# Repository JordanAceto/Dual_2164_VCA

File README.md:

# SSI2164 based dual VCA PCB

## [SCHEMATIC](https://github.com/JordanAceto/Dual_2164_VCA/blob/master/main_pcb/construction_docs/dual_VCA_schematic.pdf)

## Features:
- Two independent linear VCAs
- Manual offset controls
- Attenuated CV inputs
- Unity gain at +5 volts CV
- AC/DC coupling selected by solder jumper
- Designed to either use board mounted pots and jacks which affix directly to a panel, or mount to a bracket and wire by hand
- There is a 10hp pcb front panel, for a cheap and cheerful panel option.

## Status of the project:

Task | Status |
---------|--------------|
Schematic capture | &#9745;
PCB layout | &#9745;
Test build | &#9745;
Safe to order boards| &#9745;

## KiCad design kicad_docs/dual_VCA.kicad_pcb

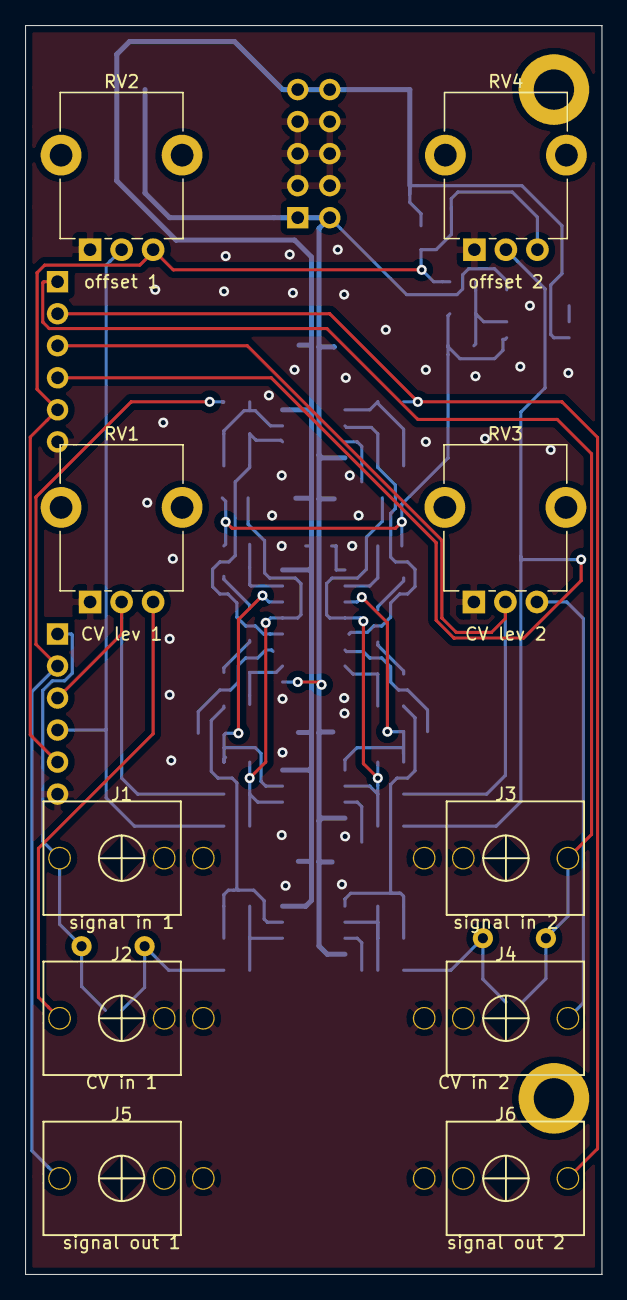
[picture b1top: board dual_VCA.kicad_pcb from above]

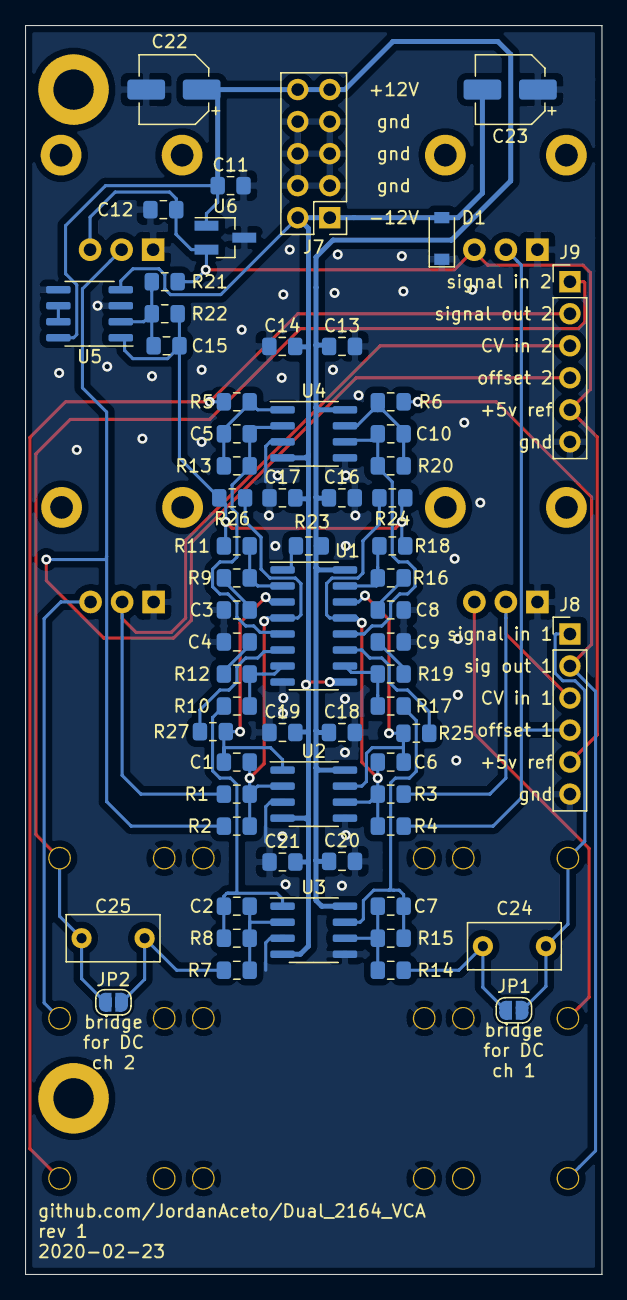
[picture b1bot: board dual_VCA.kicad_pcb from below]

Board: 2 copper layers, 45.7 x 99.1 mm, 74 parts (64 on the bottom side), 42 nets.

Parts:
C1, C5, C6, C10: 100pF; C_0805_2012Metric_Pad1.15x1.40mm_HandSolder
C2, C7: 22pF; C_0805_2012Metric_Pad1.15x1.40mm_HandSolder
C3, C4, C8, C9: 560pF; C_0805_2012Metric_Pad1.15x1.40mm_HandSolder
C11, C12, C13, C14, C15, C16, C17, C18, C19, C20, C21: 100nF; C_0805_2012Metric_Pad1.15x1.40mm_HandSolder
C22, C23: 10uF; CP_Elec_5x5.4
C24, C25: 470nF; C_Rect_L7.2mm_W3.5mm_P5.00mm_FKS2_FKP2_MKS2_MKP2
D1: BAT48; D_SOD-123
J1: signal_in_1; PJ301M-12
J2: CV_in_1; PJ301M-12
J3: signal_in_2; PJ301M-12
J4: CV_in_2; PJ301M-12
J5: signal_out_1; PJ301M-12
J6: signal_out_2; PJ301M-12
J7: power_input; PinHeader_2x05_P2.54mm_Vertical
J8, J9: Conn_01x06; PinHeader_1x06_P2.54mm_Vertical
JP1, JP2: AC/DC coupling; SolderJumper-2_P1.3mm_Open_RoundedPad1.0x1.5mm
R1, R2, R3, R4, R7, R8, R11, R14, R15, R18: 100k; R_0805_2012Metric_Pad1.15x1.40mm_HandSolder
R5, R6: 1k; R_0805_2012Metric_Pad1.15x1.40mm_HandSolder
R9, R12, R16, R19: 510; R_0805_2012Metric_Pad1.15x1.40mm_HandSolder
R10, R13, R17, R20: 30k; R_0805_2012Metric_Pad1.15x1.40mm_HandSolder
R21, R22: 10k; R_0805_2012Metric_Pad1.15x1.40mm_HandSolder
R23: R; R_0805_2012Metric_Pad1.15x1.40mm_HandSolder
R24, R26: 10M; R_0805_2012Metric_Pad1.15x1.40mm_HandSolder
R25, R27: 4k7; R_0805_2012Metric_Pad1.15x1.40mm_HandSolder
RV1, RV2, RV3, RV4: 100k; Potentiometer_Alpha_RD901F-40-00D_Single_Vertical_CircularH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
U1: SSM2164; SOIC-16_3.9x9.9mm_P1.27mm
U2, U3, U4, U5: TL072; SOIC-8_3.9x4.9mm_P1.27mm
U6: MAX6035xxUR50; SOT-23_Handsoldering

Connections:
+5VA: C12.1, J8.5, J9.5, R21.2, RV2.3, RV4.3, U6.2
+12V: C11.1, C13.1, C16.1, C18.1, C20.1, C22.1, J7.9, J7.10, R23.1, U1.16, U2.8, U3.8, U4.8, U5.8, U6.1
-5VA: C15.1, R11.2, R18.2, R22.1, R24.2, R26.2, U5.1
-12V: C14.2, C17.2, C19.2, C21.2, C23.2, D1.2, J7.1, J7.2, U1.9, U2.4, U3.4, U4.4, U5.4
/CV_in_1: J8.3, R3.2, RV1.2
/CV_in_2: J9.3, R1.2, RV3.2
/VCA_1/VCA_1_CV_summing_node_i_in: C6.2, R3.1, R4.1, R24.1, U1.13, U2.6
/VCA_1/VCA_1_signal_v_in: C24.1, JP1.2, R14.2
/VCA_1/VCA_1_signal_v_out: C10.1, R6.2, R20.1, U4.7
/VCA_2/VCA_2_CV_summing_node_i_in: C1.2, R1.1, R2.1, R26.1, U1.4, U2.2
/VCA_2/VCA_2_signal_v_in: C25.1, JP2.2, R7.2
/VCA_2/VCA_2_signal_v_out: C5.1, R5.2, R13.1, U4.1
/offset_in_1: J8.4, R4.2, RV2.2
/offset_in_2: J9.4, R2.2, RV4.2
/signal_in_1: C24.2, J1.3, J8.1, JP1.1
/signal_in_2: C25.2, J3.3, J9.1, JP2.1
/signal_out_1: J5.3, J8.2, R6.1
/signal_out_2: J6.3, J9.2, R5.1
GND: C3.2, C4.2, C8.2, C9.2, C11.2, C12.2, C13.2, C14.1, C16.2, C17.1, C18.2, C19.1, C20.2, C21.1, C22.2, C23.1, D1.1, J1.1, J1.2, J2.1, J2.2, J3.1, J3.2, J4.1, J4.2, J5.1, J6.1, J7.3, J7.4, J7.5, J7.6, J7.7, J7.8, J8.6, J9.6, RV1.1, RV2.1, RV3.1, RV4.1, U1.8, U2.3, U2.5, U3.3, U3.5, U4.3, U4.5, U5.3, U5.5, U6.3
unnamed: C1.1, R27.2, U1.3, U2.1
unnamed: C2.1, R8.1, R10.2, U3.1
unnamed: C2.2, R7.1, R8.2, U3.2
unnamed: C3.1, R9.2
unnamed: C4.1, R12.2
unnamed: C5.2, R13.2, U1.5, U4.2
unnamed: C6.1, R25.2, U1.14, U2.7
unnamed: C7.1, R15.1, R17.2, U3.7
unnamed: C7.2, R14.1, R15.2, U3.6
unnamed: C8.1, R16.2
unnamed: C9.1, R19.2
unnamed: C10.2, R20.2, U1.12, U4.6
unnamed: C15.2, R21.1, R22.2, U5.2
unnamed: J2.3, RV1.3
unnamed: J4.3, RV3.3
unnamed: R10.1, R12.1, U1.7
unnamed: R9.1, R11.1, U1.2
unnamed: R16.1, R18.1, U1.15
unnamed: R17.1, R19.1, U1.10
unnamed: R23.2, U1.1
unnamed: R25.1, U1.11
unnamed: R27.1, U1.6
unnamed: U5.6, U5.7

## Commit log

2020-02-09 add AC/DC coupling caps and jumper
2020-02-09 update pics to reflect AC/DC coupling
2020-02-09 add readme
2020-02-09 Create LICENSE
2020-02-09 add values to r's, add r's to CV circuit
2020-02-09 update pcb png's
2020-02-09 add schematic pdf
2020-02-23 add github url to pcb silkscreen
2020-07-13 add panel, generate interactive BOM
2020-08-06 add front panel, update readme
2020-08-06 add rendered pic of front panel
2020-08-15 check off built-and-tested and documentation boxes
2021-12-09 reorganize pics and readmes
2022-01-06 give schematic better name
2022-01-06 add finished pic, update readme
